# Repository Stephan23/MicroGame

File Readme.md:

MicroGame
=========
In this repository you find the firmware and hardware design for the
"MicroGame", an open-source game based on the keyboard function of the Arduino Micro.

Snake
-----

'0' -> Snake, 'X' -> Targel, 'O' -> Border

Tetris
------
Coming soon.

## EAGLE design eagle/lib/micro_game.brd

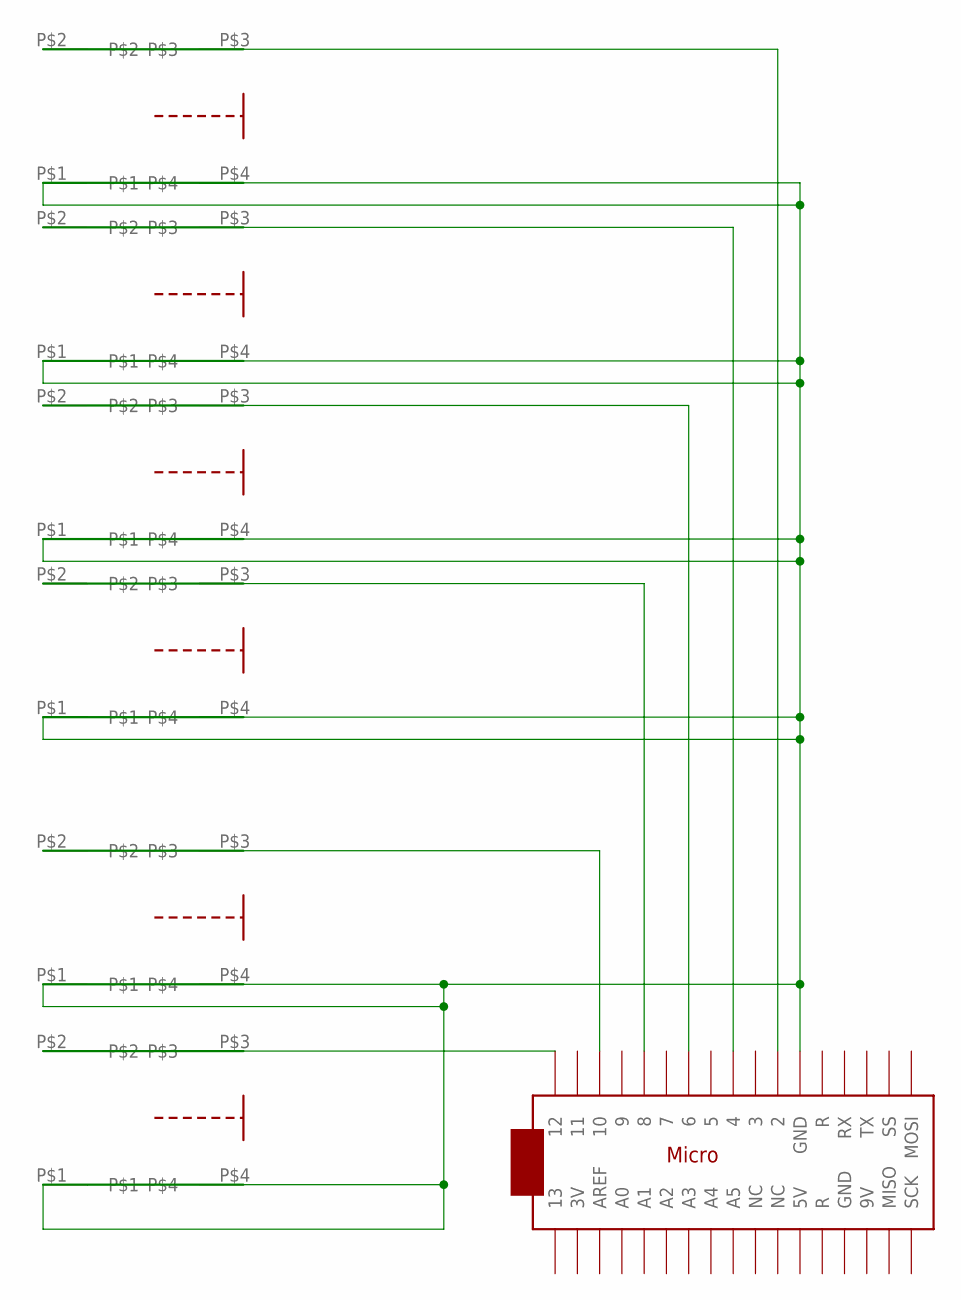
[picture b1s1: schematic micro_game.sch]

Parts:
U$1: ARDUINOMICRO
U$2, U$3, U$4, U$5, U$6, U$7: MICRO_GAME_SWITCH

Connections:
GND: U$1.P$21 (GND), U$2.P$1, U$2.P$4, U$3.P$1, U$3.P$4, U$4.P$1, U$4.P$4, U$5.P$1, U$5.P$4, U$6.P$1, U$6.P$4, U$7.P$1, U$7.P$4
unnamed: U$1.P$11 (2), U$4.P$3
unnamed: U$1.P$9 (4), U$2.P$3
unnamed: U$1.P$7 (6), U$3.P$3
unnamed: U$1.P$5 (8), U$5.P$3
unnamed: U$1.P$3 (10), U$6.P$3
unnamed: U$1.P$1 (12), U$7.P$3

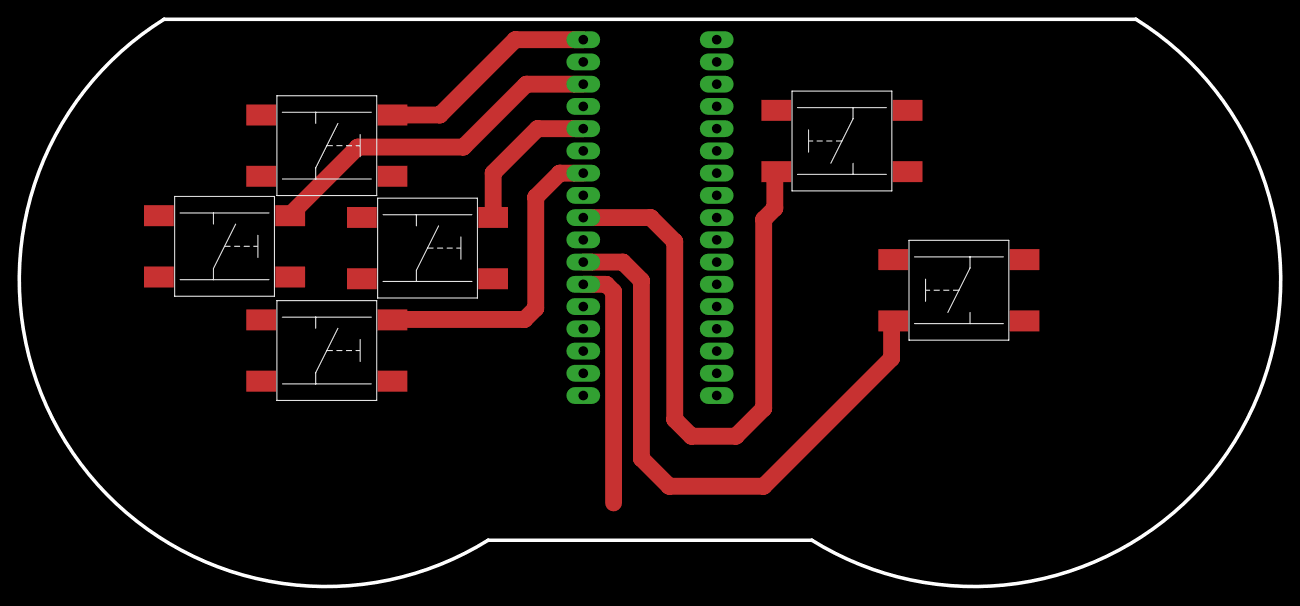
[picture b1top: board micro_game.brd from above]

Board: 2 copper layers, 144.1 x 64.8 mm, 7 parts (1 on the bottom side), 7 nets.

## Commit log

2015-06-22 init
2015-06-22 readme
2015-06-22 snake gif
